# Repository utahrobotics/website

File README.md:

# website
USR website written with Node and React and other cool jazz like that.

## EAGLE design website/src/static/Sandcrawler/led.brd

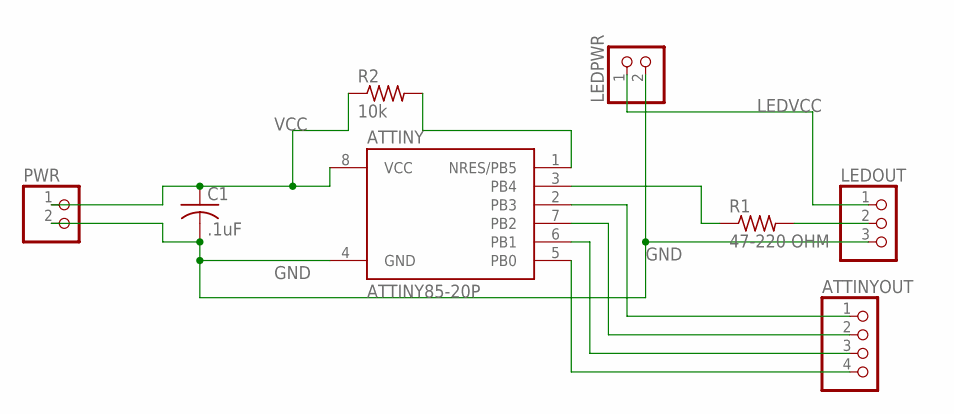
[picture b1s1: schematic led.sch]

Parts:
ATTINY: ATTINY85-20P; PDIP08_300MIL
ATTINYOUT: PINHD-1X4; 1X04
C1: .1uF; C050-025X075
LEDOUT: PINHD-1X3; 1X03
LEDPWR: PINHD-1X2; 1X02
PWR: PINHD-1X2; 1X02
R1: 47-220 OHM; 0207/12
R2: 10k; 0207/12

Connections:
GND: ATTINY.4 (GND), C1.2, LEDOUT.3, LEDPWR.2, PWR.2
LEDVCC: LEDOUT.1, LEDPWR.1
unnamed: ATTINY.2 (PB3), ATTINYOUT.1
unnamed: ATTINY.7 (PB2), ATTINYOUT.2
unnamed: ATTINY.3 (PB4), R1.1
unnamed: LEDOUT.2, R1.2
unnamed: ATTINY.6 (PB1), ATTINYOUT.3
unnamed: ATTINY.5 (PB0), ATTINYOUT.4
unnamed: ATTINY.1 (NRES/PB5), R2.2
VCC: ATTINY.8 (VCC), C1.1, PWR.1, R2.1

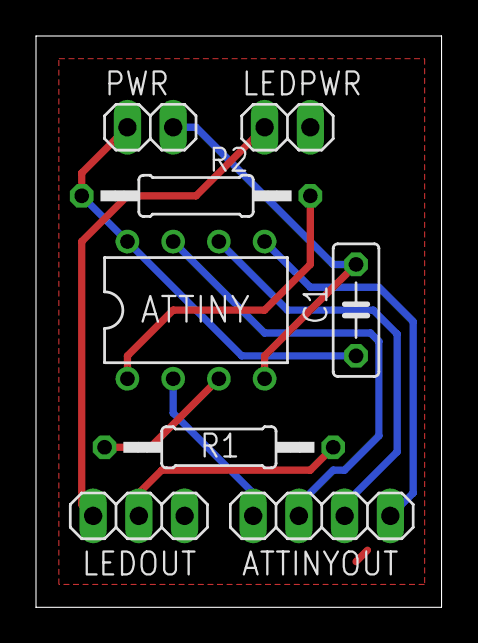
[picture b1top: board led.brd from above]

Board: 2 copper layers, 22.5 x 31.7 mm, 8 parts (0 on the bottom side), 10 nets.

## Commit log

2019-07-20 did lots of neat stuff
2019-07-20 added al ittle to sponsors page
2019-08-18 new pages, ui improvements
2019-08-19 added animations
2019-08-21 I don't remember what I changed.
2019-09-14 added info to resources
2019-09-14 added more resources
2019-09-14 added picture of Amy
2020-01-08 added some about info
2020-01-09 added content, fixed scroll events
2020-01-13 working on REST API to connect to AMEE
2020-01-14 rad buttons
2020-01-19 added more robot descriptions
2020-10-05 added some sponsor images
2020-10-05 added download link for minecraft mod to resources page
2020-10-06 updates from the server
2020-10-07 added to minecraft mod resources. Created initial pages for classes
2020-10-07 fixed extra import, causing exception
2021-01-13 added some videos and a small local database for storing comments
2021-01-14 Changed http requests system
2021-02-21 updated videos
2021-03-07 updated Turing version
2021-03-08 added robot anim
2021-03-09 added stuff to contact page.
2021-11-17 Added support for posting and getting ips from the server
2021-11-17 reversed the display order of ips
2021-11-17 added ssid field
2021-11-19 works live
2021-11-19 better ip insertion
2021-11-19 fixed bug
2022-10-06 Fixed typo and updated contacts
2022-11-15 added Programming
2022-11-15 added line breaks
2022-11-15 added links
2022-11-15 corrected mailtos
2023-05-06 Bump ua-parser-js from 0.7.31 to 0.7.35 in /website
    Bumps [ua-parser-js](https://github.com/faisalman/ua-parser-js) from 0.7.31 to 0.7.35.
    - [Release notes](https://github.com/faisalman/ua-parser-js/releases)
    - [Changelog](https://github.com/faisalman/ua-parser-js/blob/master/changelog.md)
    - [Commits](https://github.com/faisalman/ua-parser-js/compare/0.7.31...0.7.35)
    ---
    updated-dependencies:
2023-05-06 Bump decode-uri-component from 0.2.0 to 0.2.2 in /website
    Bumps [decode-uri-component](https://github.com/SamVerschueren/decode-uri-component) from 0.2.0 to 0.2.2.
    - [Release notes](https://github.com/SamVerschueren/decode-uri-component/releases)
    - [Commits](https://github.com/SamVerschueren/decode-uri-component/compare/v0.2.0...v0.2.2)
    ---
    updated-dependencies:
    - dependency-name: decode-uri-component
2023-05-06 Bump http-cache-semantics and npm in /website
    Removes [http-cache-semantics](https://github.com/kornelski/http-cache-semantics). It's no longer used after updating ancestor dependency [npm](https://github.com/npm/cli). These dependencies need to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
    Removes `http-cache-semantics`
    Updates `npm` from 6.14.15 to 9.6.6
    - [Release notes](https://github.com/npm/cli/releases)
    - [Changelog](https://github.com/npm/cli/blob/latest/CHANGELOG.md)
    - [Commits](https://github.com/npm/cli/compare/v6.14.15...v9.6.6)
